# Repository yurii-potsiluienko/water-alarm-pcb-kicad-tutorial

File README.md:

# Water alarm PCB

## Overview

This project was created by following a KiCad tutorial to learn the fundamentals of PCB design in KiCad.

The PCB integrates several components, including a buzzer, an LED, a MOSFET, a screw terminal, a DC jack, resistors and capacitors.

## Components

* [Buzzer](https://www.digikey.ca/en/products/detail/pui-audio-inc/AI-3035-TT-12V-R/9083403?s=N4IgTCBcDaIGxwBwFoCMcCsZkDkAiIAugL5A)
* [MOSFET](https://www.digikey.ca/en/products/detail/diotec-semiconductor/2N7000/13164314?s=N4IgTCBcDaICwA4DsCC0YBySAMuDCAKqhgCIgC6AvkA)
* [Screw terminal](https://www.digikey.ca/en/products/detail/adam-tech/EBAA-02-C/13586872?s=N4IgTCBcDa4AwFYDsBaAogIQIJZXMKAwigHIAiIAugL5A)
* [DC jack](https://www.digikey.ca/en/products/detail/same-sky-formerly-cui-devices/PJ-037A/1644545?s=N4IgTCBcDaIMIAUC0AGAzAdgIJIHIBEQBdAXyA)
* Resistors, capacitors, LED

## Features

* Indicator LED for status

## Tools Used

* KiCad (schematic capture and PCB layout)
* GitHub for documentation

## What I Learned

* Creating schematics in KiCad
* PCB component placement
* Trace routing and board organization

## Images

### Schematic

### 3D View

## Tutorial Reference

This project was created by following this tutorial:

- [KiCad 9.0 - Getting Started](https://www.youtube.com/watch?v=0WCi1rhueH4&list=PLEBQazB0HUyQ5YJSdCBb79orXaR3Uk5vm)

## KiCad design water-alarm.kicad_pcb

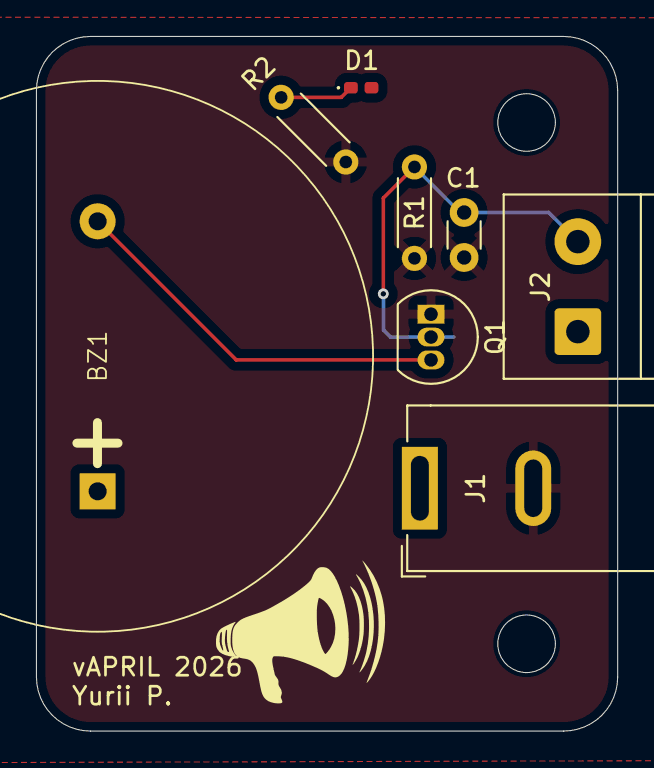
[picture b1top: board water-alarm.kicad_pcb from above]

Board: 2 copper layers, 32.3 x 38.6 mm, 8 parts (0 on the bottom side), 5 nets.

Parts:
BZ1: Buzzer; Buzzer_D30mm_H20mm_P15mm__668-1652-ND__AI-3035-TT-12V-R
C1: 1nF; C_Disc_D3.0mm_W1.6mm_P2.50mm
D1: LED_Small_Filled; LED_0402_1005Metric_Pad0.77x0.64mm_HandSolder
J1: Jack-DC; BarrelJack_GCT_DCJ200-10-A_Horizontal
J2: Screw_Terminal_01x02; TerminalBlock_Phoenix_PT-1,5-2-5.0-H_1x02_P5.00mm_Horizontal
Q1: 2N7000; TO-92_Inline
R1: 10M; R_Axial_DIN0204_L3.6mm_D1.6mm_P5.08mm_Horizontal
R2: 6.8K; R_Axial_DIN0204_L3.6mm_D1.6mm_P5.08mm_Horizontal

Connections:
/Gate: C1.1, J2.2, Q1.2 (G), R1.1
GND: C1.2, J1.2, Q1.1 (S), R1.2, R2.2
unnamed: BZ1.2 (-), Q1.3 (D)
unnamed: D1.1 (K), R2.1
VCC: BZ1.1 (+), D1.2 (A), J1.1, J2.1

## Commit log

2026-04-03 Revise README for Arduino Nano sensor interface PCB
    Updated project title and added detailed overview, components, features, tools used, learning outcomes, images, and tutorial reference.
2026-04-03 Remove content from blank file
2026-04-03 Edited README
